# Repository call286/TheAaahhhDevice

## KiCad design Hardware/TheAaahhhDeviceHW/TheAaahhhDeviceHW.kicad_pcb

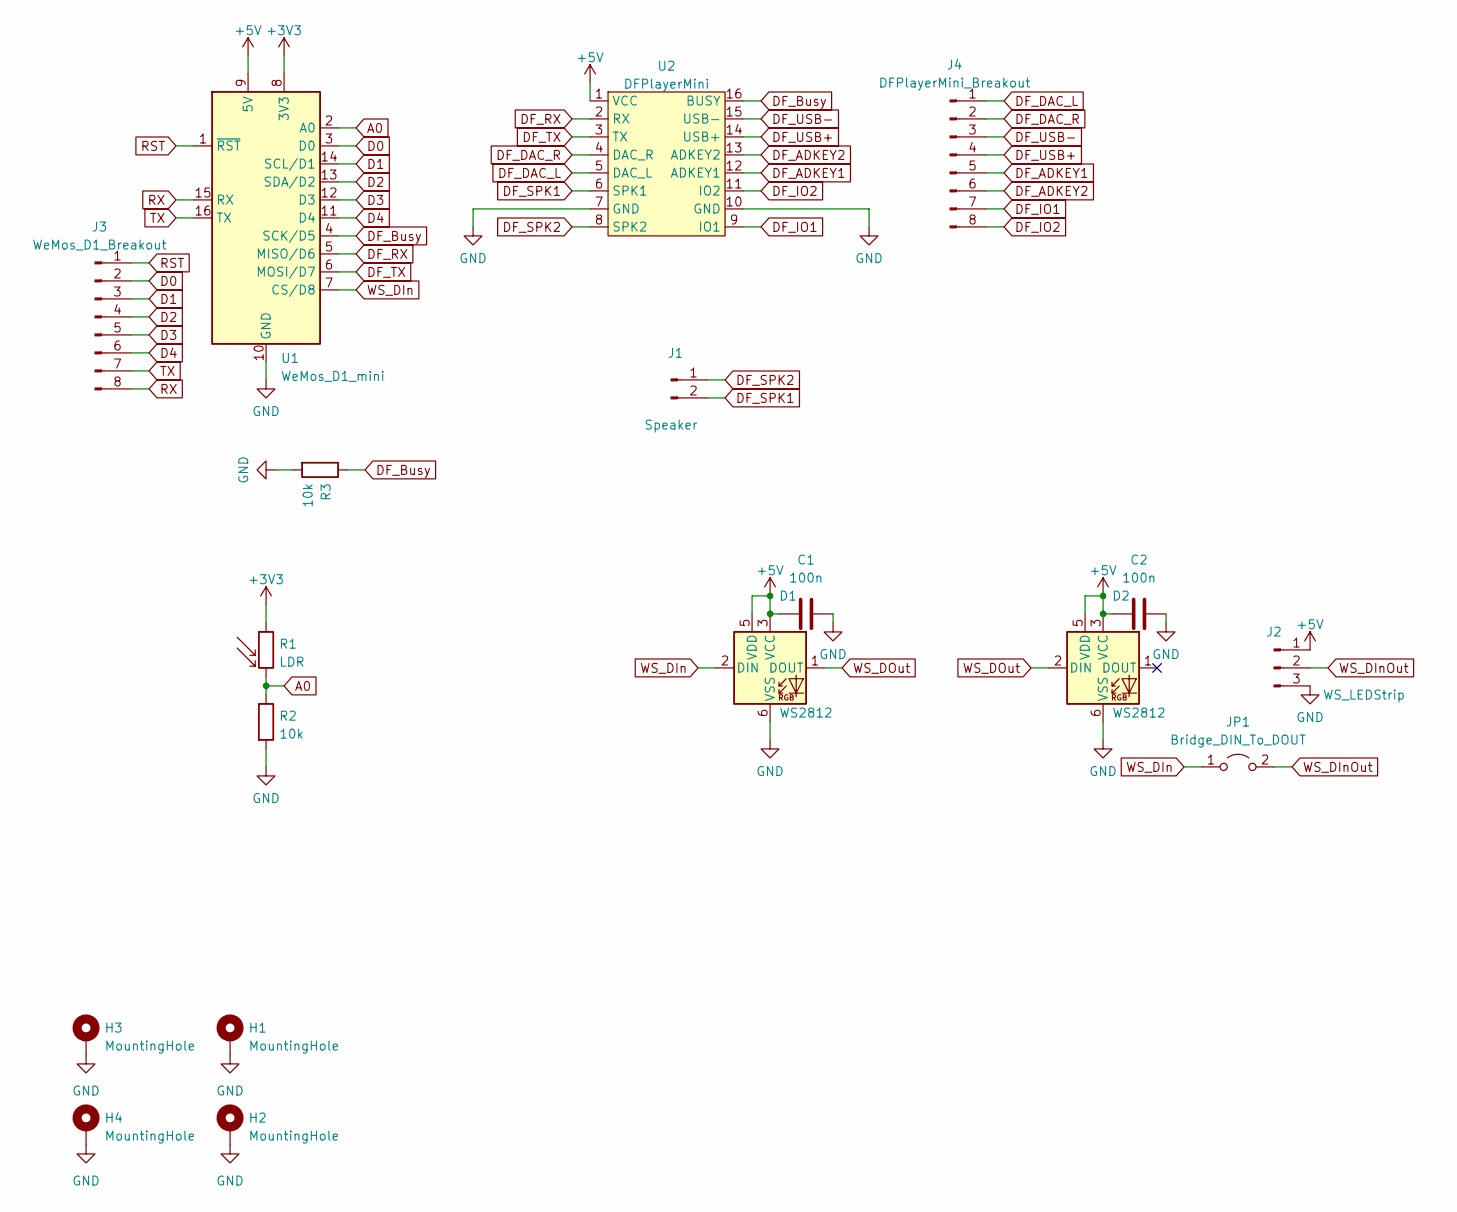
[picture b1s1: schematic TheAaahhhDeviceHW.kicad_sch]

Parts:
C1, C2: 100n; C_0805_2012Metric_Pad1.18x1.45mm_HandSolder
D1, D2: WS2812; LED_WS2812+SMD
H1, H2, H3, H4: MountingHole; MountingHole_3.2mm_M3_Pad_Via
J1: Speaker; PinHeader_1x02_P2.54mm_Vertical
J2: WS_LEDStrip; PinHeader_1x03_P2.54mm_Vertical
J3: WeMos_D1_Breakout; PinHeader_1x08_P2.54mm_Vertical
J4: DFPlayerMini_Breakout; PinHeader_1x08_P2.54mm_Vertical
JP1: Bridge_DIN_To_DOUT; SolderJumper-2_P1.3mm_Open_RoundedPad1.0x1.5mm
R1: LDR; R_LDR_5.1x4.3mm_P3.4mm_Vertical
R2, R3: 10k; R_Axial_DIN0207_L6.3mm_D2.5mm_P10.16mm_Horizontal
U1: WeMos_D1_mini; WEMOS_D1_mini_light
U2: DFPlayerMini; DFPlayer

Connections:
+3V3: R1.1, U1.8 (3V3)
+5V: C1.2, C2.2, D1.3 (VCC), D1.5 (VDD), D2.3 (VCC), D2.5 (VDD), J2.1, U1.9 (5V), U2.1 (VCC)
A0: R1.2, R2.1, U1.2 (A0)
D0: J3.2, U1.3 (D0)
D1: J3.3, U1.14 (SCL/D1)
D2: J3.4, U1.13 (SDA/D2)
D3: J3.5, U1.12 (D3)
D4: J3.6, U1.11 (D4)
DF_ADKEY1: J4.5, U2.12 (ADKEY1)
DF_ADKEY2: J4.6, U2.13 (ADKEY2)
DF_Busy: R3.1, U1.4 (SCK/D5), U2.16 (BUSY)
DF_DAC_L: J4.1, U2.5 (DAC_L)
DF_DAC_R: J4.2, U2.4 (DAC_R)
DF_IO1: J4.7, U2.9 (IO1)
DF_IO2: J4.8, U2.11 (IO2)
DF_RX: U1.5 (MISO/D6), U2.2 (RX)
DF_SPK1: J1.2, U2.6 (SPK1)
DF_SPK2: J1.1, U2.8 (SPK2)
DF_TX: U1.6 (MOSI/D7), U2.3 (TX)
DF_USB+: J4.4, U2.14 (USB+)
DF_USB-: J4.3, U2.15 (USB-)
GND: C1.1, C2.1, D1.6 (VSS), D2.6 (VSS), H1.1, H2.1, H3.1, H4.1, J2.3, R2.2, R3.2, U1.10 (GND), U2.7 (GND), U2.10 (GND)
RST: J3.1, U1.1 (~RST)
RX: J3.8, U1.15 (RX)
TX: J3.7, U1.16 (TX)
WS_DIn: D1.2 (DIN), JP1.1 (A), U1.7 (CS/D8)
WS_DInOut: J2.2, JP1.2 (B)
WS_DOut: D1.1 (DOUT), D2.2 (DIN)

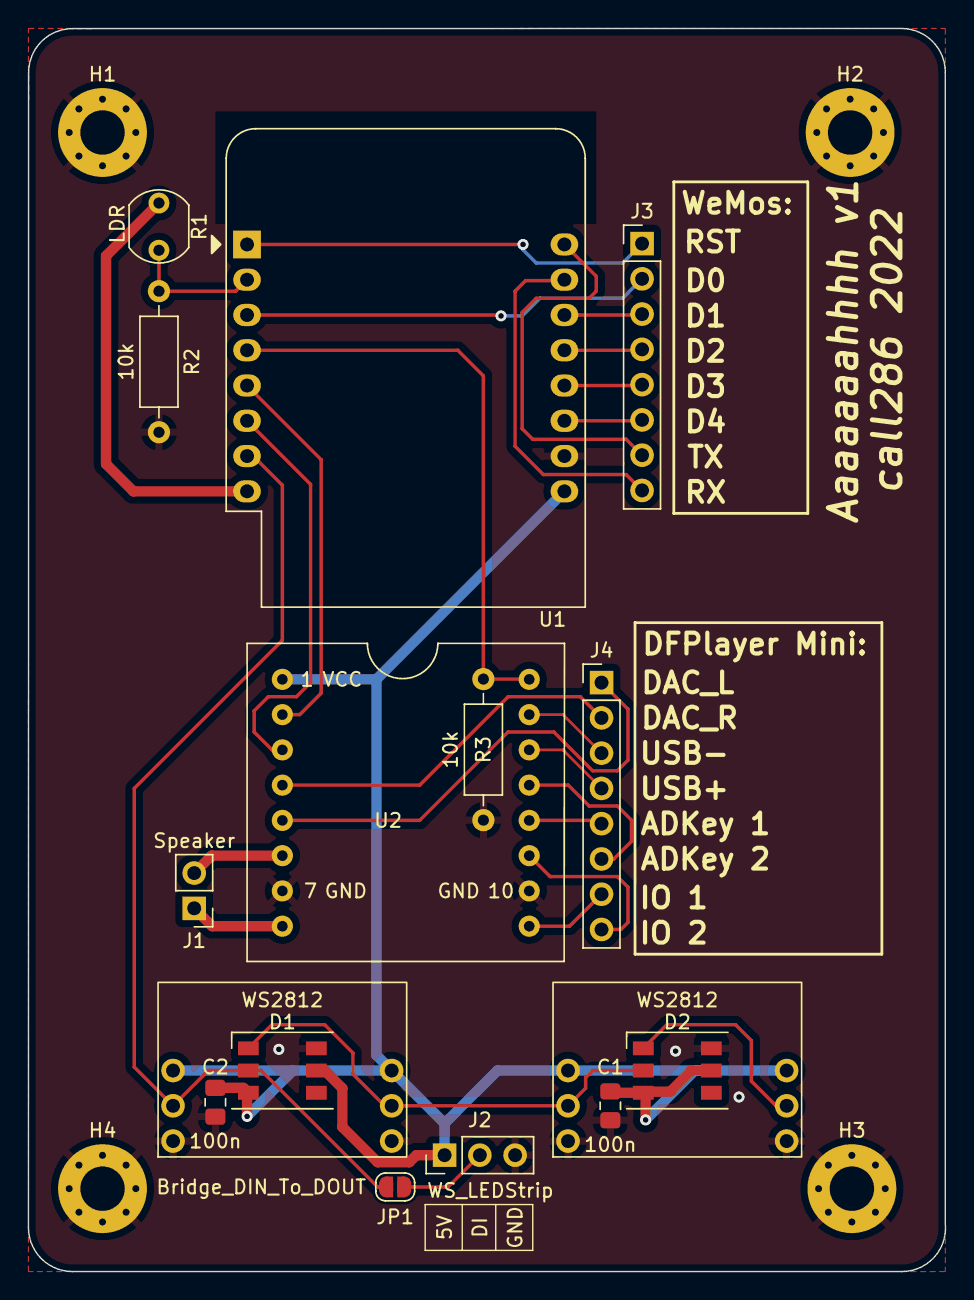
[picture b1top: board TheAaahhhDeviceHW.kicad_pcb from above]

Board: 2 copper layers, 66.1 x 89.5 mm, 18 parts (0 on the bottom side), 28 nets.

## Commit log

2022-09-18 Initial version, playing
2022-09-25 src/main.cpp
2022-09-27 2022-09-27
2022-09-27 Added DFPlayer Code
2022-10-01 Switched to Adafruit Neopixel Lib Used code from https://arduino.stackexchange.com/questions/10357/arduino-with-ws2812-using-adafruit-neopixel-library-fade-in-out-different-patter for fading
2022-10-10 KiCAD begin
2022-10-17 2022-10-17
2022-10-23 2022-10-23
2022-10-24 2022-10-24
